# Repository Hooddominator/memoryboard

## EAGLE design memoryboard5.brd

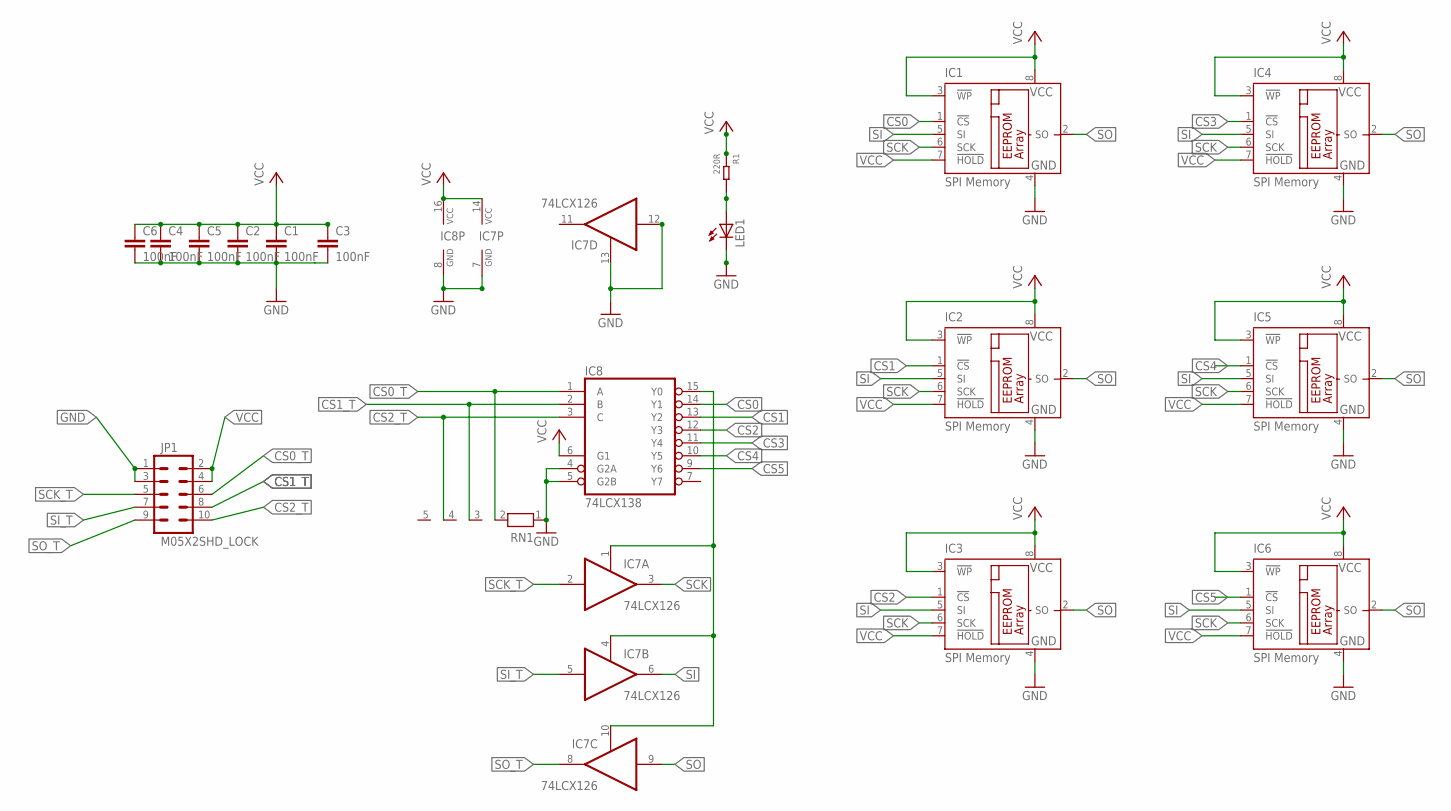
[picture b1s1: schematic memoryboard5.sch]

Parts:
C1, C2, C3, C4, C5, C6: 100nF; C0805
IC1, IC2, IC3, IC4, IC5, IC6: SPI Memory; DIL8
IC7: 74LCX126; DIL14
IC8: 74LCX138; DIL16
JP1: M05X2SHD_LOCK; 2X5-SHROUDED_LOCK
LED1: LED3MM
R1: 220R; R0805
RN1: RN04; RN-5

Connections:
CS0: IC1.1 (!CS), IC8.14 (Y1)
CS0_T: IC8.1 (A), JP1.6, RN1.2
CS1: IC2.1 (!CS), IC8.13 (Y2)
CS1_T: IC8.2 (B), JP1.8, RN1.3
CS2: IC3.1 (!CS), IC8.12 (Y3)
CS2_T: IC8.3 (C), JP1.10, RN1.4
CS3: IC4.1 (!CS), IC8.11 (Y4)
CS4: IC5.1 (!CS), IC8.10 (Y5)
CS5: IC6.1 (!CS), IC8.9 (Y6)
GND: C1.2, C2.2, C3.2, C4.2, C5.2, C6.2, IC1.4 (GND), IC2.4 (GND), IC3.4 (GND), IC4.4 (GND), IC5.4 (GND), IC6.4 (GND), IC7.7 (GND), IC7.12 (I), IC7.13 (OE), IC8.4 (G2A), IC8.5 (G2B), IC8.8 (GND), JP1.1, JP1.3, LED1.K (C), RN1.1
unnamed: LED1.A, R1.2
SCK: IC1.6 (SCK), IC2.6 (SCK), IC3.6 (SCK), IC4.6 (SCK), IC5.6 (SCK), IC6.6 (SCK), IC7.3 (O)
SCK_T: IC7.2 (I), JP1.5
SI: IC1.5 (SI), IC2.5 (SI), IC3.5 (SI), IC4.5 (SI), IC5.5 (SI), IC6.5 (SI), IC7.6 (O)
SI_T: IC7.5 (I), JP1.7
SO: IC1.2 (SO), IC2.2 (SO), IC3.2 (SO), IC4.2 (SO), IC5.2 (SO), IC6.2 (SO), IC7.9 (I)
SO_T: IC7.8 (O), JP1.9
SPI_ENABLE: IC7.1 (OE), IC7.4 (OE), IC7.10 (OE), IC8.15 (Y0)
VCC: C1.1, C2.1, C3.1, C4.1, C5.1, C6.1, IC1.3 (!WP), IC1.7 (!HOLD), IC1.8 (VCC), IC2.3 (!WP), IC2.7 (!HOLD), IC2.8 (VCC), IC3.3 (!WP), IC3.7 (!HOLD), IC3.8 (VCC), IC4.3 (!WP), IC4.7 (!HOLD), IC4.8 (VCC), IC5.3 (!WP), IC5.7 (!HOLD), IC5.8 (VCC), IC6.3 (!WP), IC6.7 (!HOLD), IC6.8 (VCC), IC7.14 (VCC), IC8.6 (G1), IC8.16 (VCC), JP1.2, JP1.4, R1.1

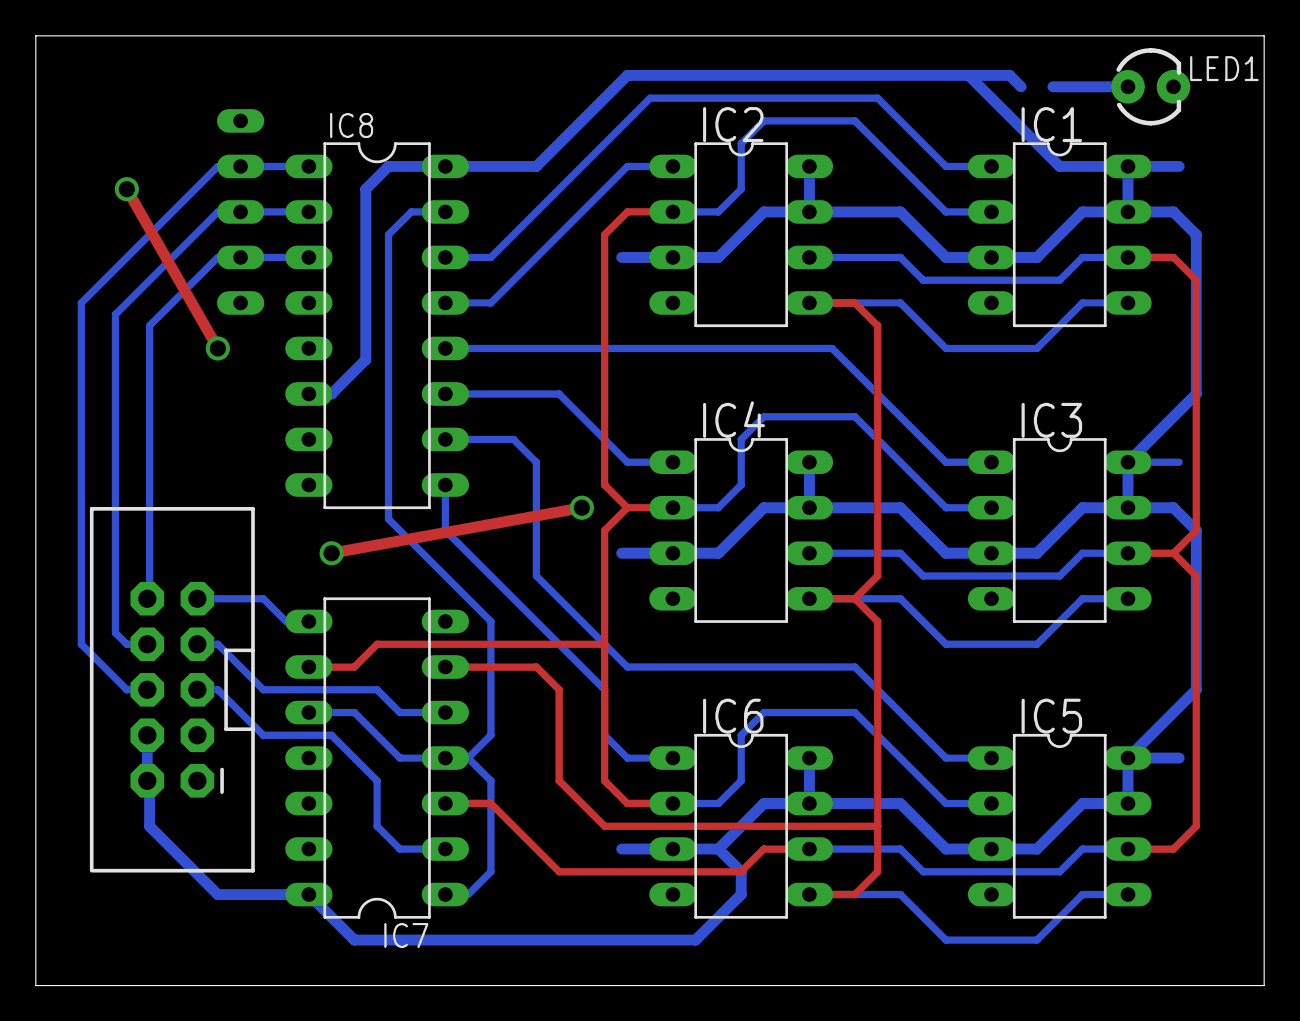
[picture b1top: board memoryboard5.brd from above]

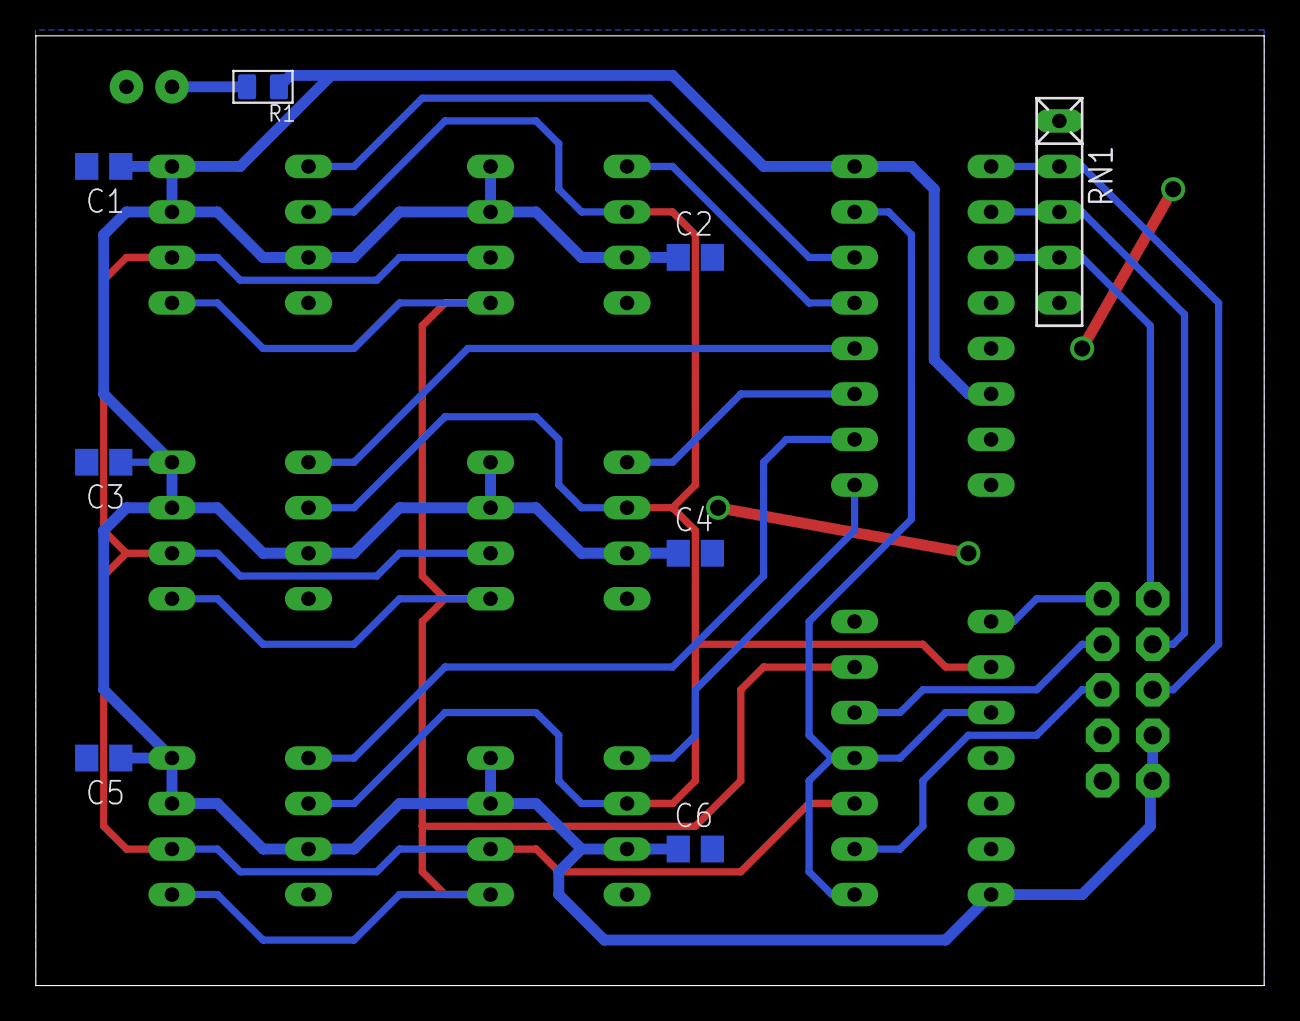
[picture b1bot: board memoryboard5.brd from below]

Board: 2 copper layers, 68.6 x 53.0 mm, 18 parts (8 on the bottom side), 19 nets.

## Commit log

2017-11-27 added dip-version
